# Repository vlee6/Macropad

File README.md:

# ATmega32U4 Macropad

For my first-ever PCB project, I've designed a 9 key low-profile macropad with a rotary encoder and oled screen. My intention was to keep costs minimal while retaining features found in most contemporary macropads. I began this journey after soldering my very own low-profile Lily58 build. While the Lily58 takes up minimal desk space and is very ergonomic, I found myself suffering from the small key count and lack of special features such as rotary encoders. Since I couldn't find any affordable alternative online, I set out to build my very own low-profile macropad to complete my desk setup.

### Specs:
- ATmega32U4 Microcontroller
- 9 Kailh Hotswap Sockets (Low-profile Choc V1)
- WS2812B-2020 South-Facing Per-Key RGB Lighting
- Bourns PEC11R Rotary Encoder Switch
- 128x32 Oled I2C Display Module
- Easy-to-assemble 3D printed case
- (soon to be) VIA Compatible

### How is this different from the other macropads?
- Low-profile switches (like the Choc V1s I'm using in this build) are 40% shorter than regular mechanical keyboard switches.
- All components are directly soldered onto the board, no pro-micro (or equivalent devkit) necessary
- Per-key RGB lighting, not just underglow
- Estimated total cost of $30 to make, including all components and switches

### Assembly Instructions:
You will need...
- A switch for the reset buttom
- 9 Kailh Choc V1 switches of your choice
- 9 Choc V1 1U keycaps, I'm using clear Chosfox ones but MBK Choc keycaps will also work
- 9 WS2812B-2020 LEDs
- PEC11R-4015F-S0024 rotary encoder or equivalent
- A soldering setup
- Various electrical components that can be found on the [full parts list](https://docs.google.com/spreadsheets/d/1zmoziKfNFVxXU5fcjUS9J8uJfZayq2XkwIlthU0o6MI/edit?usp=sharing)

1. The board can be ordered with the production files in this repository (BOM and CPL included). If you are manufacturing with JLCPCB, have them assemble the bottom side (you will only need to solder the LEDs on the top side).
2. After printing out the top and bottom case from the STLs in this repository, they can be sandwiched to the PCB with four 4mm M2 screws (inserted from the bottom). If your PCB and case is aligned properly, the switches will snap in easily.

### Image Dump

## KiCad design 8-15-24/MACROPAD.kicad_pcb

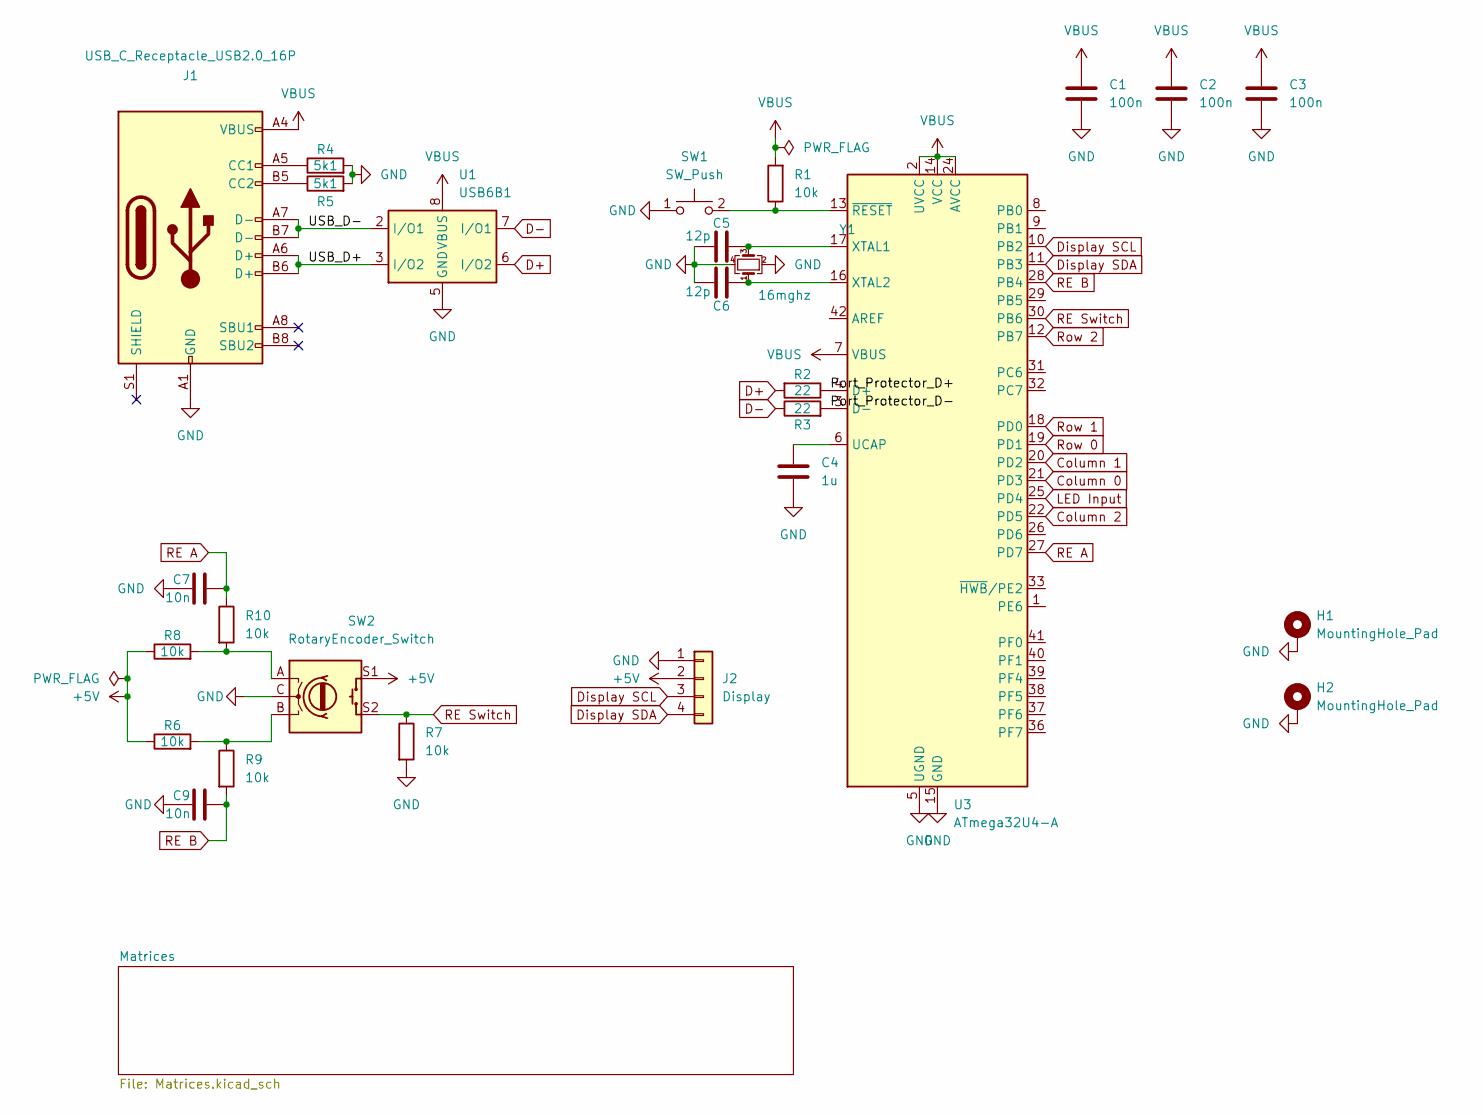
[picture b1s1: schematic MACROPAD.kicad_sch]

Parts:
C1, C2, C3: 100n; C_0402_1005Metric
C4: 1u; C_0402_1005Metric
C5, C6: 12p; C_0402_1005Metric
C7, C9: 10n; C_0402_1005Metric
H1, H2: MountingHole_Pad; MountingHole_KB
J1: USB_C_Receptacle_USB2.0_16P; USB_C_HRO_TYPE-C-31-M-12
J2: Display; SSD1306_LCD_Display_128x32
R1, R6, R7, R8, R9, R10: 10k; R_0402_1005Metric
R2, R3: 22; R_0402_1005Metric
R4, R5: 5k1; R_0402_1005Metric
SW1: SW_Push; SW_Tactile_TSB008A2530A
SW2: RotaryEncoder_Switch; RotaryEncoder_Bourns_PEC11R-4xxxF-Sxxxx
U1: USB6B1; USB_Port_Protector_USB6B1
U3: ATmega32U4-A; TQFP-44_10x10mm_P0.8mm
Y1: 16mghz; Crystal_SMD_X322516MLB4SI

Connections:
+5V: J2.2, R6.1, R8.1, SW2.S1; also elsewhere on the board
/Port_Protector_D+: R2.1, U3.4 (D+)
/Port_Protector_D-: R3.2, U3.3 (D-)
/USB_D+: J1.A6 (D+), J1.B6 (D+), U1.3 (I/O2)
/USB_D-: J1.A7 (D-), J1.B7 (D-), U1.2 (I/O1)
Column 0: U3.21 (PD3); also elsewhere on the board
Column 1: U3.20 (PD2); also elsewhere on the board
Column 2: U3.22 (PD5); also elsewhere on the board
D+: R2.2, U1.6 (I/O2)
D-: R3.1, U1.7 (I/O1)
Display SCL: J2.3, U3.10 (PB2)
Display SDA: J2.4, U3.11 (PB3)
GND: C1.2, C2.2, C3.2, C4.2, C5.2, C6.2, C7.1, C9.1, H1.1, H2.1, J1.A1 (GND), J1.A12 (GND), J1.B1 (GND), J1.B12 (GND), J2.1, R4.2, R5.2, R7.2, SW1.1, SW2.C, U1.4 (GND), U1.5 (GND), U3.5 (UGND), U3.15 (GND), U3.23 (GND), U3.35 (GND), U3.43 (GND), Y1.2, Y1.4; also elsewhere on the board
LED Input: U3.25 (PD4); also elsewhere on the board
unnamed: J1.A5 (CC1), R4.1
unnamed: J1.B5 (CC2), R5.1
unnamed: R6.2, R9.1, SW2.B
unnamed: R8.2, R10.2, SW2.A
unnamed: C4.1, U3.6 (UCAP)
unnamed: C5.1, U3.17 (XTAL1), Y1.3
unnamed: C6.1, U3.16 (XTAL2), Y1.1
unnamed: R1.1, SW1.2, U3.13 (~RESET)
RE A: C7.2, R10.1, U3.27 (PD7)
RE B: C9.2, R9.2, U3.28 (PB4)
RE Switch: R7.1, SW2.S2, U3.30 (PB6)
Row 0: U3.19 (PD1); also elsewhere on the board
Row 1: U3.18 (PD0); also elsewhere on the board
Row 2: U3.12 (PB7); also elsewhere on the board
VBUS: C1.1, C2.1, C3.1, J1.A4 (VBUS), J1.A9 (VBUS), J1.B4 (VBUS), J1.B9 (VBUS), R1.2, U1.1 (VBUS), U1.8 (VBUS), U3.2 (UVCC), U3.7 (VBUS), U3.14 (VCC), U3.24 (AVCC), U3.34 (VCC), U3.44 (AVCC)

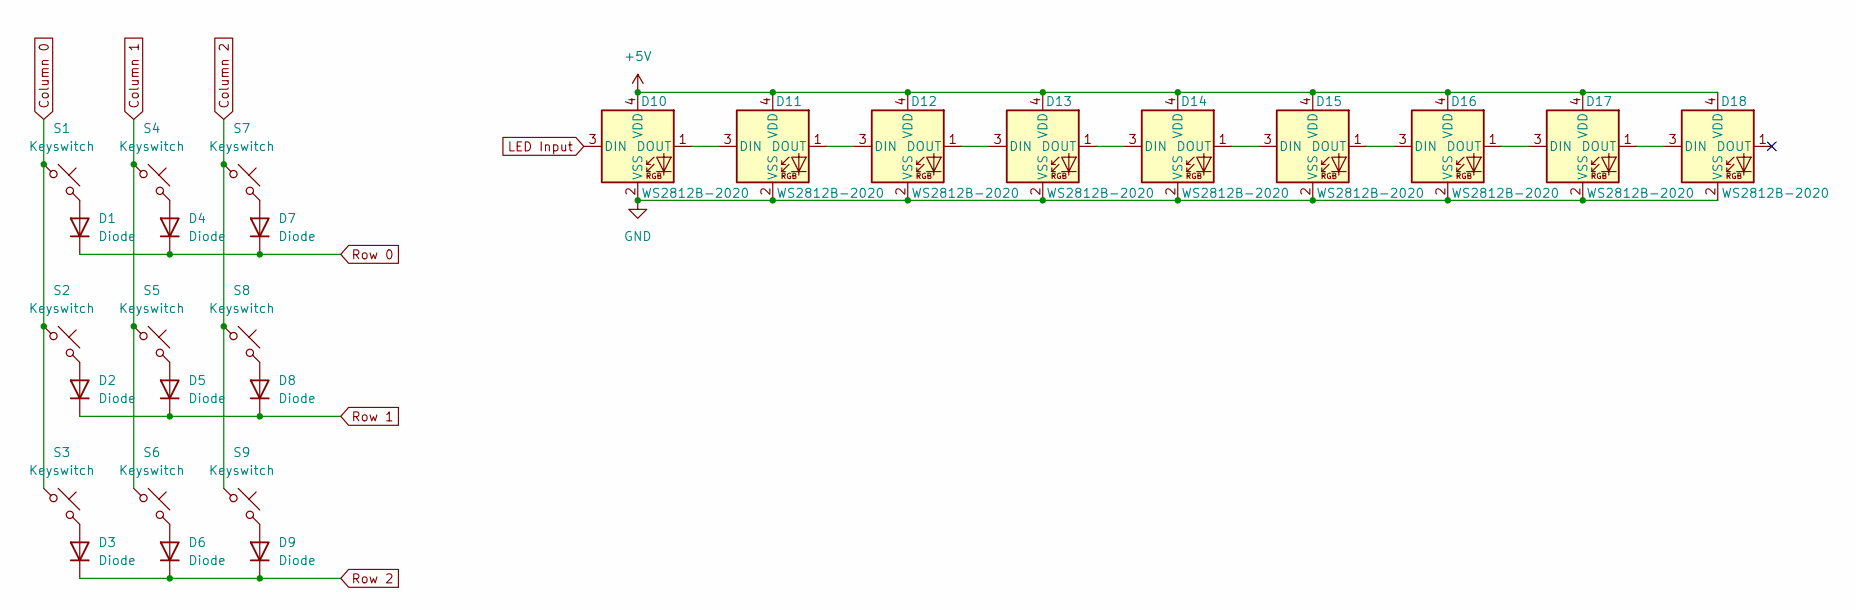
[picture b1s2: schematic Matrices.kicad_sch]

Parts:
D1, D2, D3, D4, D5, D6, D7, D8, D9: Diode; Diode_SOD-123
D10, D11, D12, D13, D14, D15, D16, D17, D18: WS2812B-2020; LED_WS2812B-2020_PLCC4_2.0x2.0mm
S1, S2, S3, S4, S5, S6, S7, S8, S9: Keyswitch; Hotswap_Choc_V1_Plated_1.00u

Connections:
+5V: D10.4 (VDD), D11.4 (VDD), D12.4 (VDD), D13.4 (VDD), D14.4 (VDD), D15.4 (VDD), D16.4 (VDD), D17.4 (VDD), D18.4 (VDD); also elsewhere on the board
Column 0: S1.1, S2.1, S3.1; also elsewhere on the board
Column 1: S4.1, S5.1, S6.1; also elsewhere on the board
Column 2: S7.1, S8.1, S9.1; also elsewhere on the board
GND: D10.2 (VSS), D11.2 (VSS), D12.2 (VSS), D13.2 (VSS), D14.2 (VSS), D15.2 (VSS), D16.2 (VSS), D17.2 (VSS), D18.2 (VSS); also elsewhere on the board
LED Input: D10.3 (DIN); also elsewhere on the board
unnamed: D1.2 (A), S1.2
unnamed: D2.2 (A), S2.2
unnamed: D3.2 (A), S3.2
unnamed: D4.2 (A), S4.2
unnamed: D5.2 (A), S5.2
unnamed: D6.2 (A), S6.2
unnamed: D7.2 (A), S7.2
unnamed: D8.2 (A), S8.2
unnamed: D9.2 (A), S9.2
unnamed: D10.1 (DOUT), D11.3 (DIN)
unnamed: D11.1 (DOUT), D12.3 (DIN)
unnamed: D12.1 (DOUT), D13.3 (DIN)
unnamed: D13.1 (DOUT), D14.3 (DIN)
unnamed: D14.1 (DOUT), D15.3 (DIN)
unnamed: D15.1 (DOUT), D16.3 (DIN)
unnamed: D16.1 (DOUT), D17.3 (DIN)
unnamed: D17.1 (DOUT), D18.3 (DIN)
Row 0: D1.1 (K), D4.1 (K), D7.1 (K); also elsewhere on the board
Row 1: D2.1 (K), D5.1 (K), D8.1 (K); also elsewhere on the board
Row 2: D3.1 (K), D6.1 (K), D9.1 (K); also elsewhere on the board

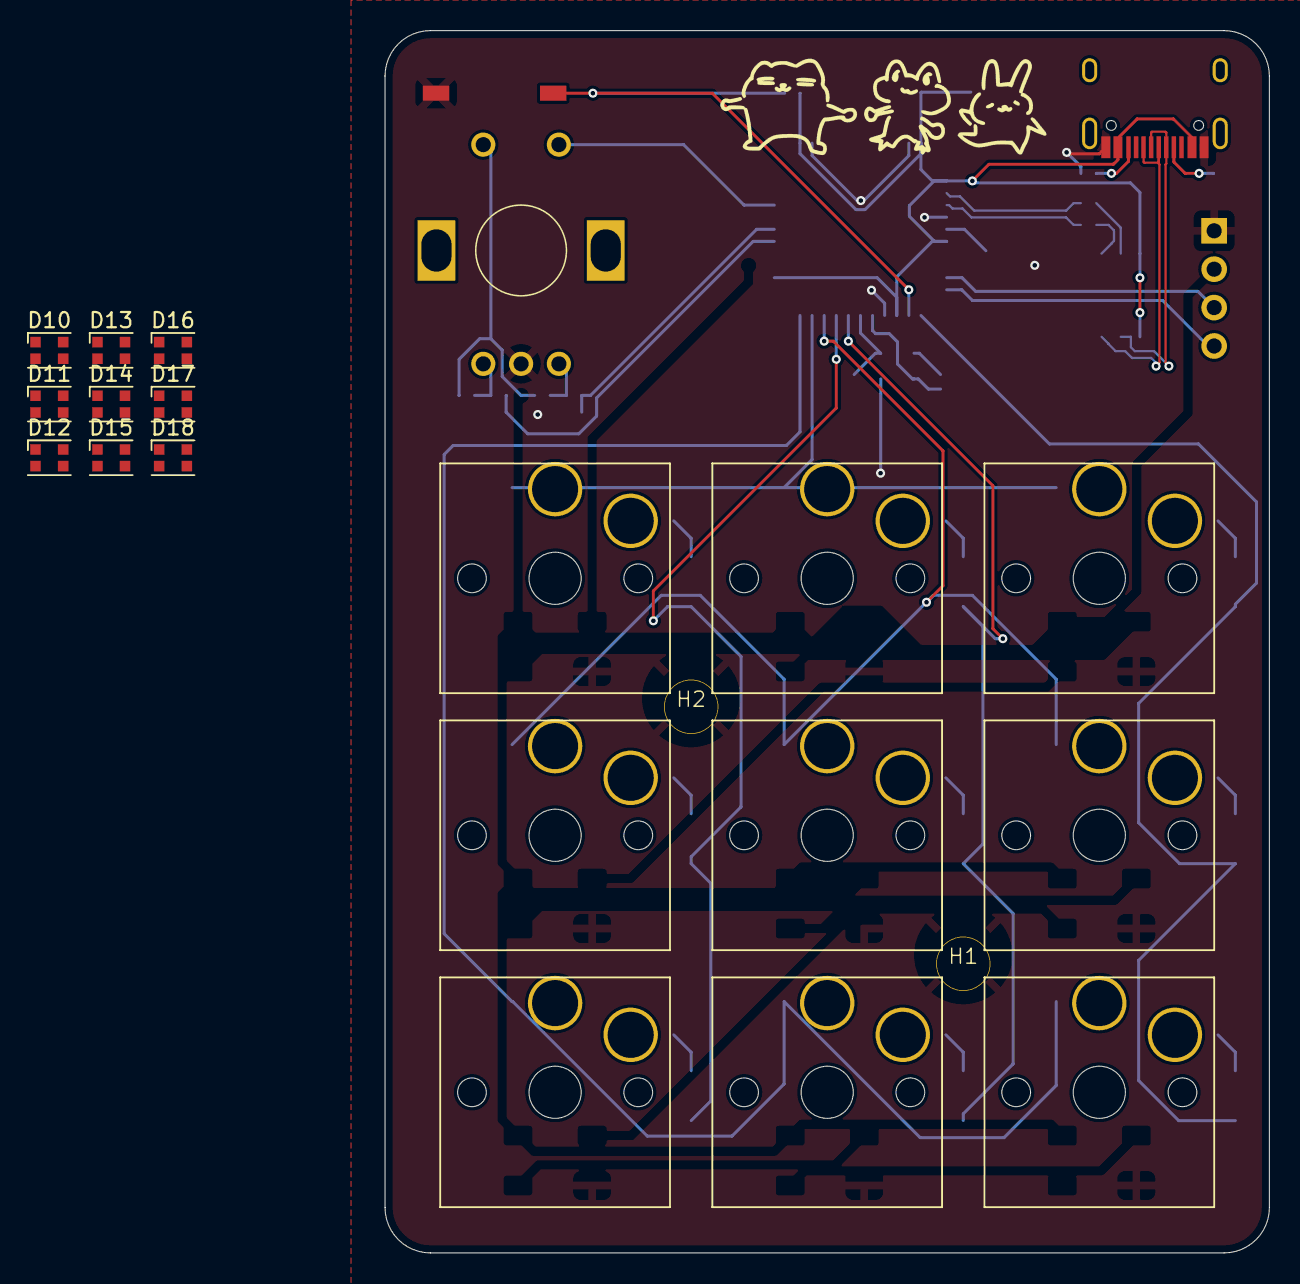
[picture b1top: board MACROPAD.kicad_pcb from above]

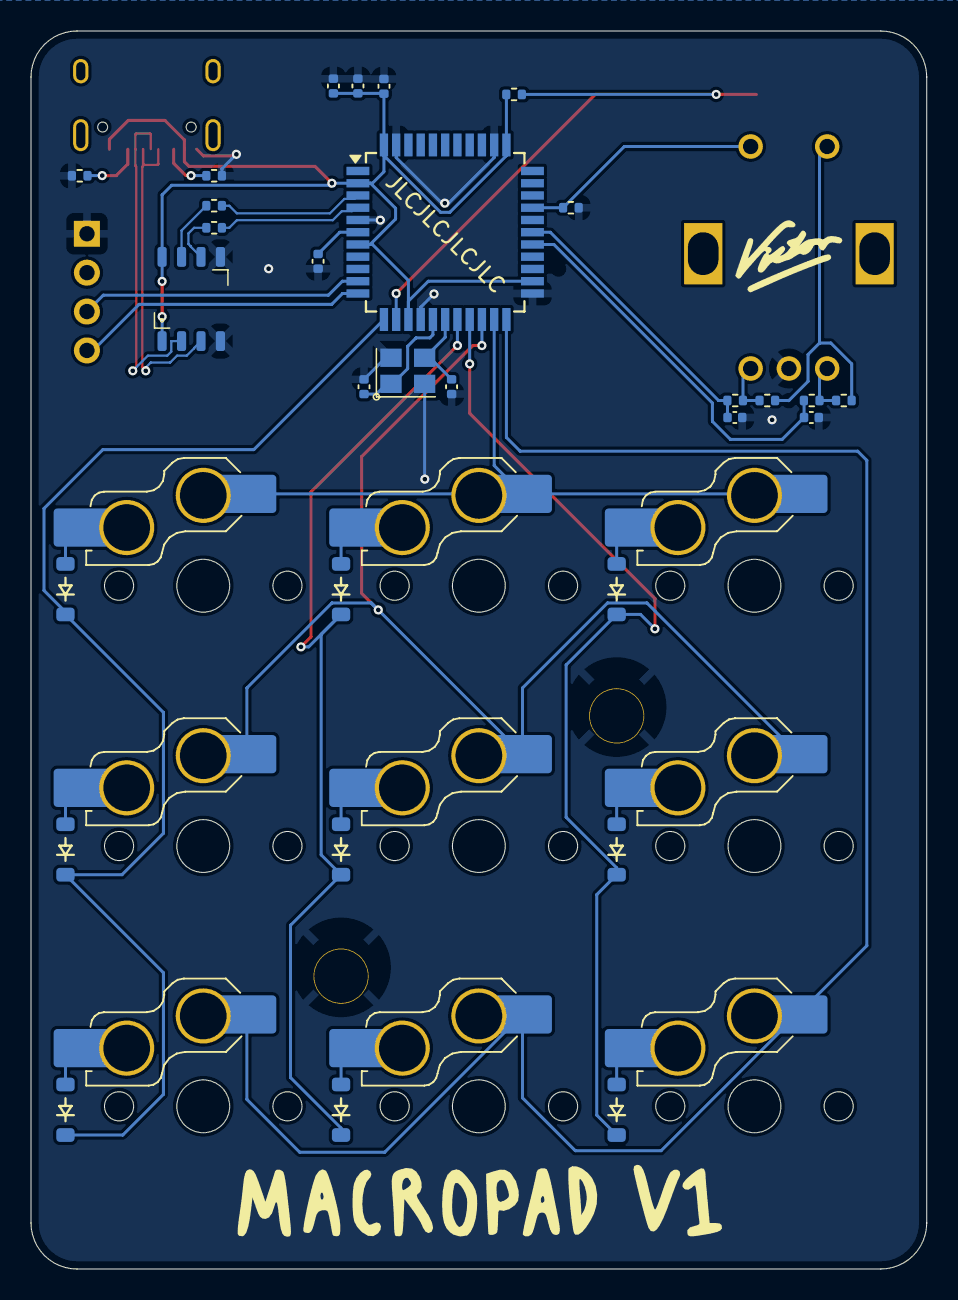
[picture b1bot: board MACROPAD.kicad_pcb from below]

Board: 2 copper layers, 58.5 x 80.9 mm, 54 parts (30 on the bottom side), 46 nets.

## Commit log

2024-08-12 Redoing macropad version control
2024-08-12 Finished routing traces and placing components
2024-08-13 Moved MCU and rounded edges
2024-08-13 Fixed issues, V1 complete
2024-08-13 Added gerbers, graphics, fixed RE button
2024-08-16 Started fixing bugs
2024-08-16 Need to figure out how to connect +5v nest to VBUS
2024-08-21 Finished design and sent out files for assembly
2024-08-21 Added case STLs
    https://cad.onshape.com/documents/7c0fd680344a7fb116117cb6/w/ed0fe4f0ce8d5604549aa17e/e/687a8a392ee8c72c6ad0a9a0?renderMode=0&uiState=66c63a2d4c2e2a4146ece0d4
2024-08-21 Added images for README
2024-08-21 Added case to images
2024-08-21 Added image with oled
2024-08-21 Need to redo cases
2024-08-21 Added updated case models
